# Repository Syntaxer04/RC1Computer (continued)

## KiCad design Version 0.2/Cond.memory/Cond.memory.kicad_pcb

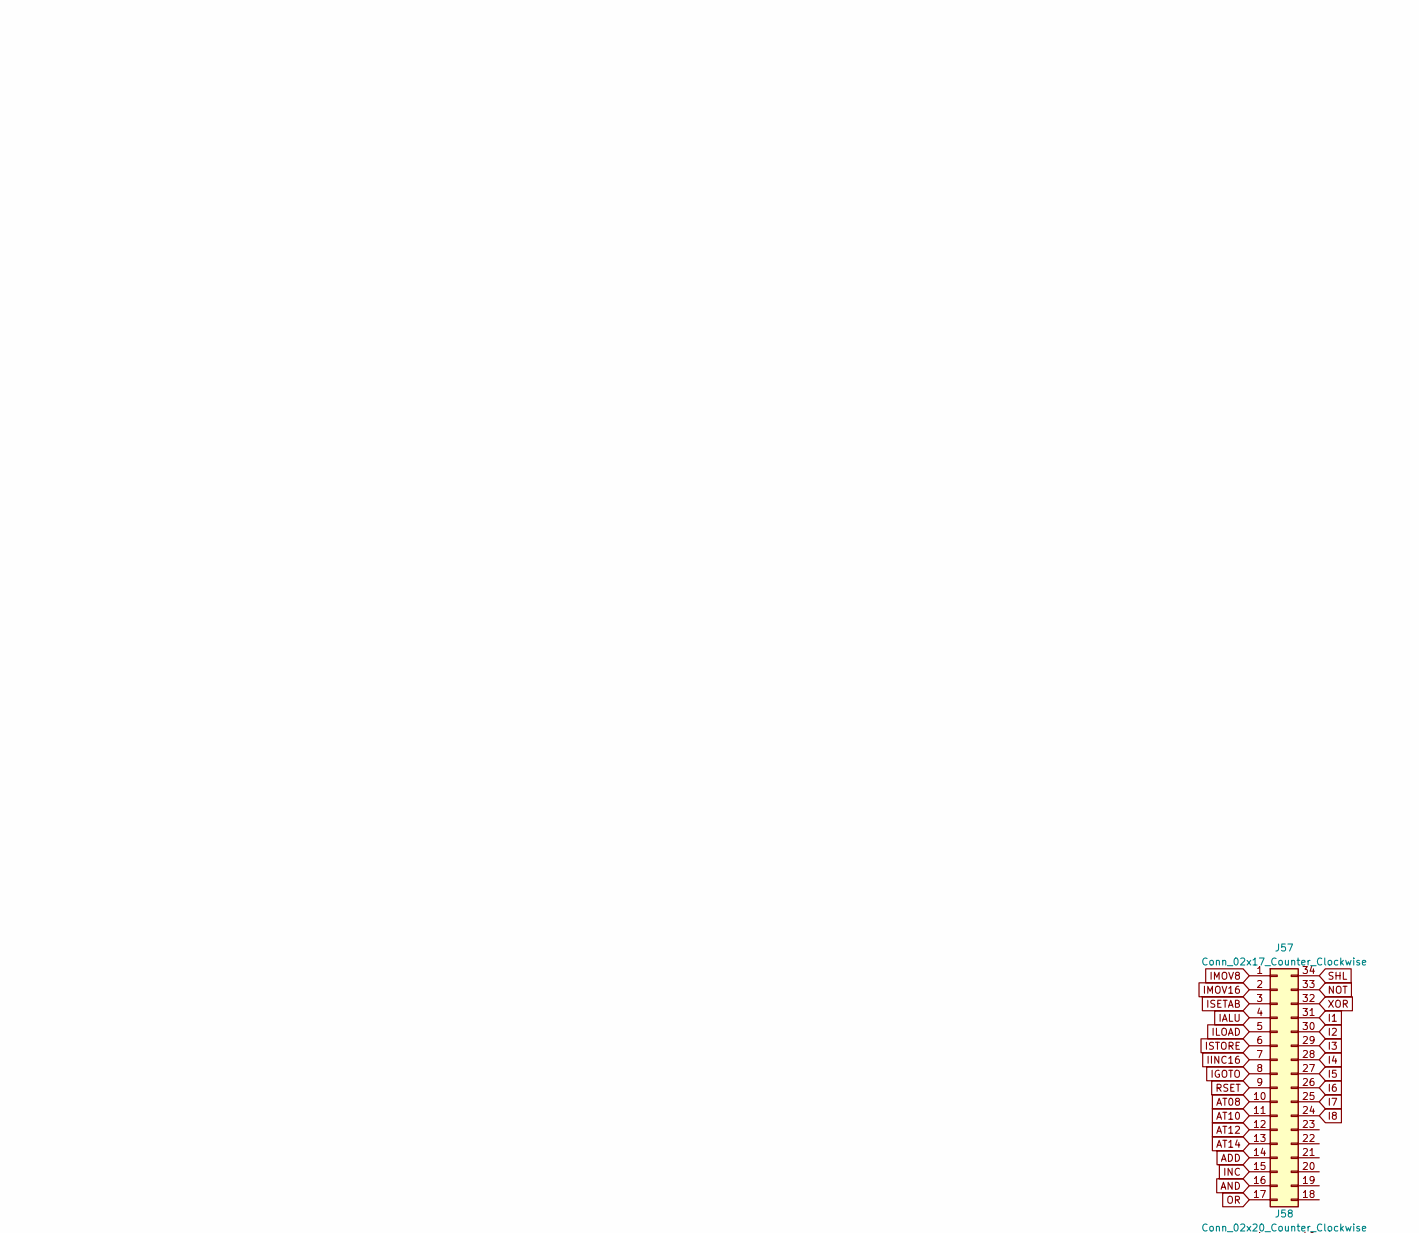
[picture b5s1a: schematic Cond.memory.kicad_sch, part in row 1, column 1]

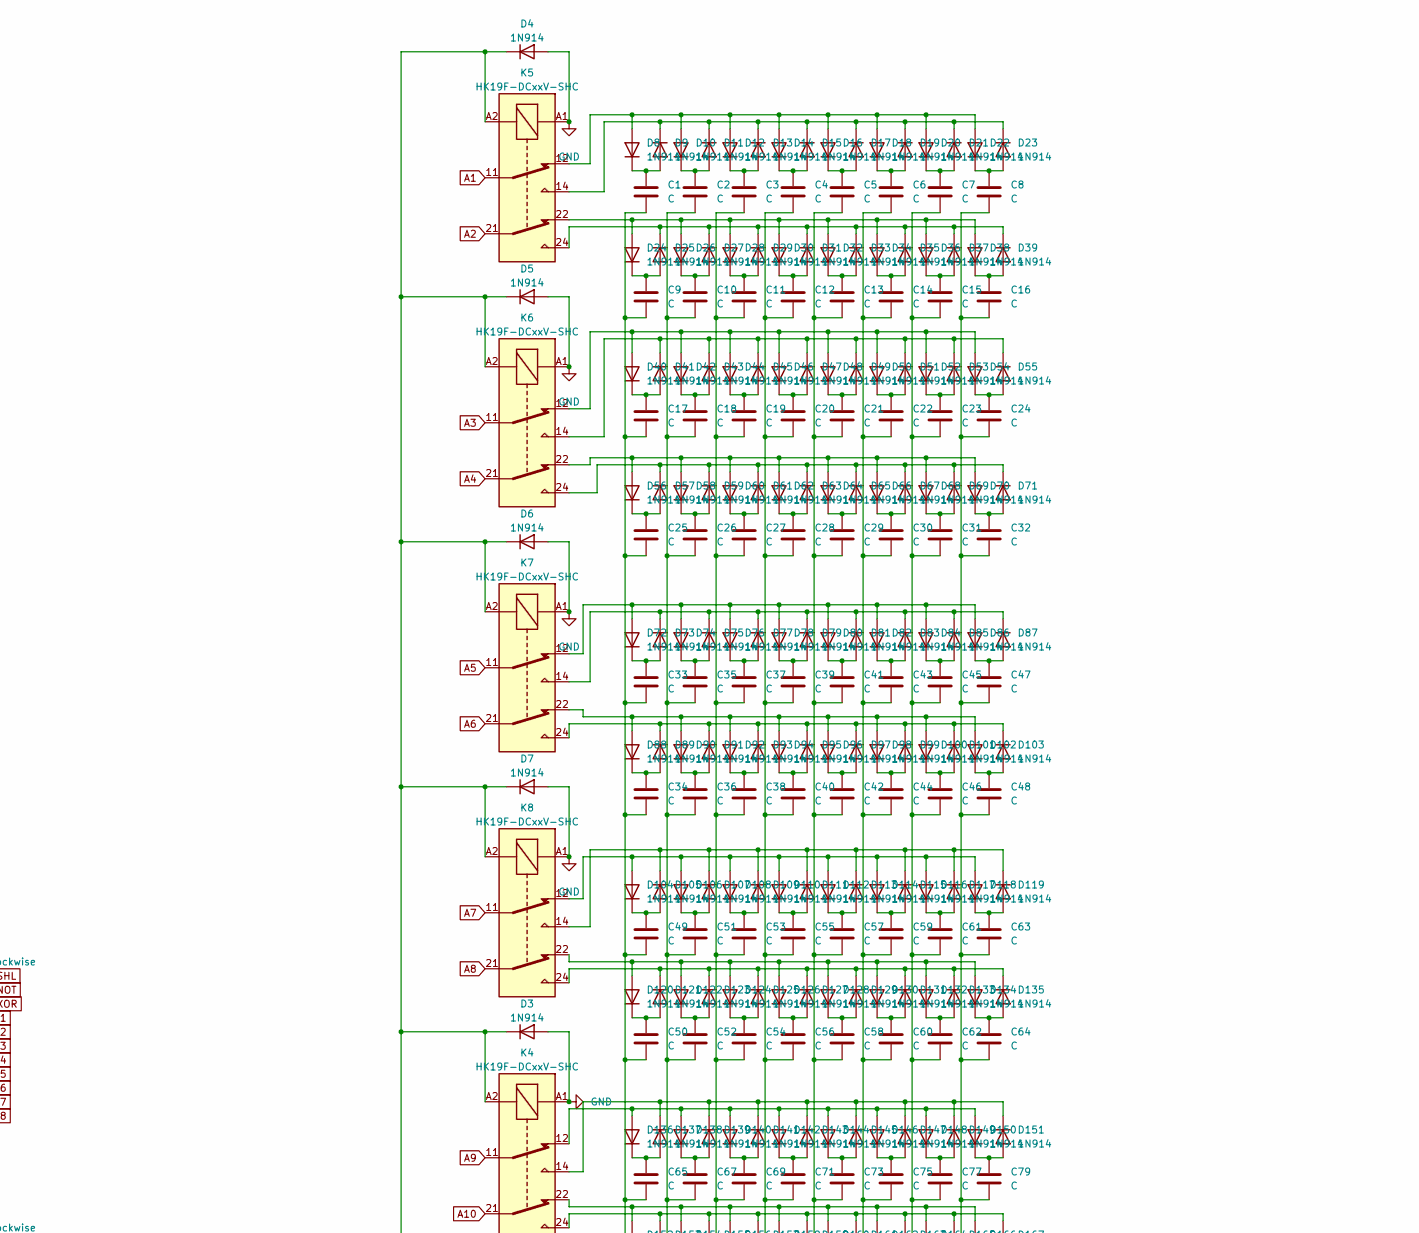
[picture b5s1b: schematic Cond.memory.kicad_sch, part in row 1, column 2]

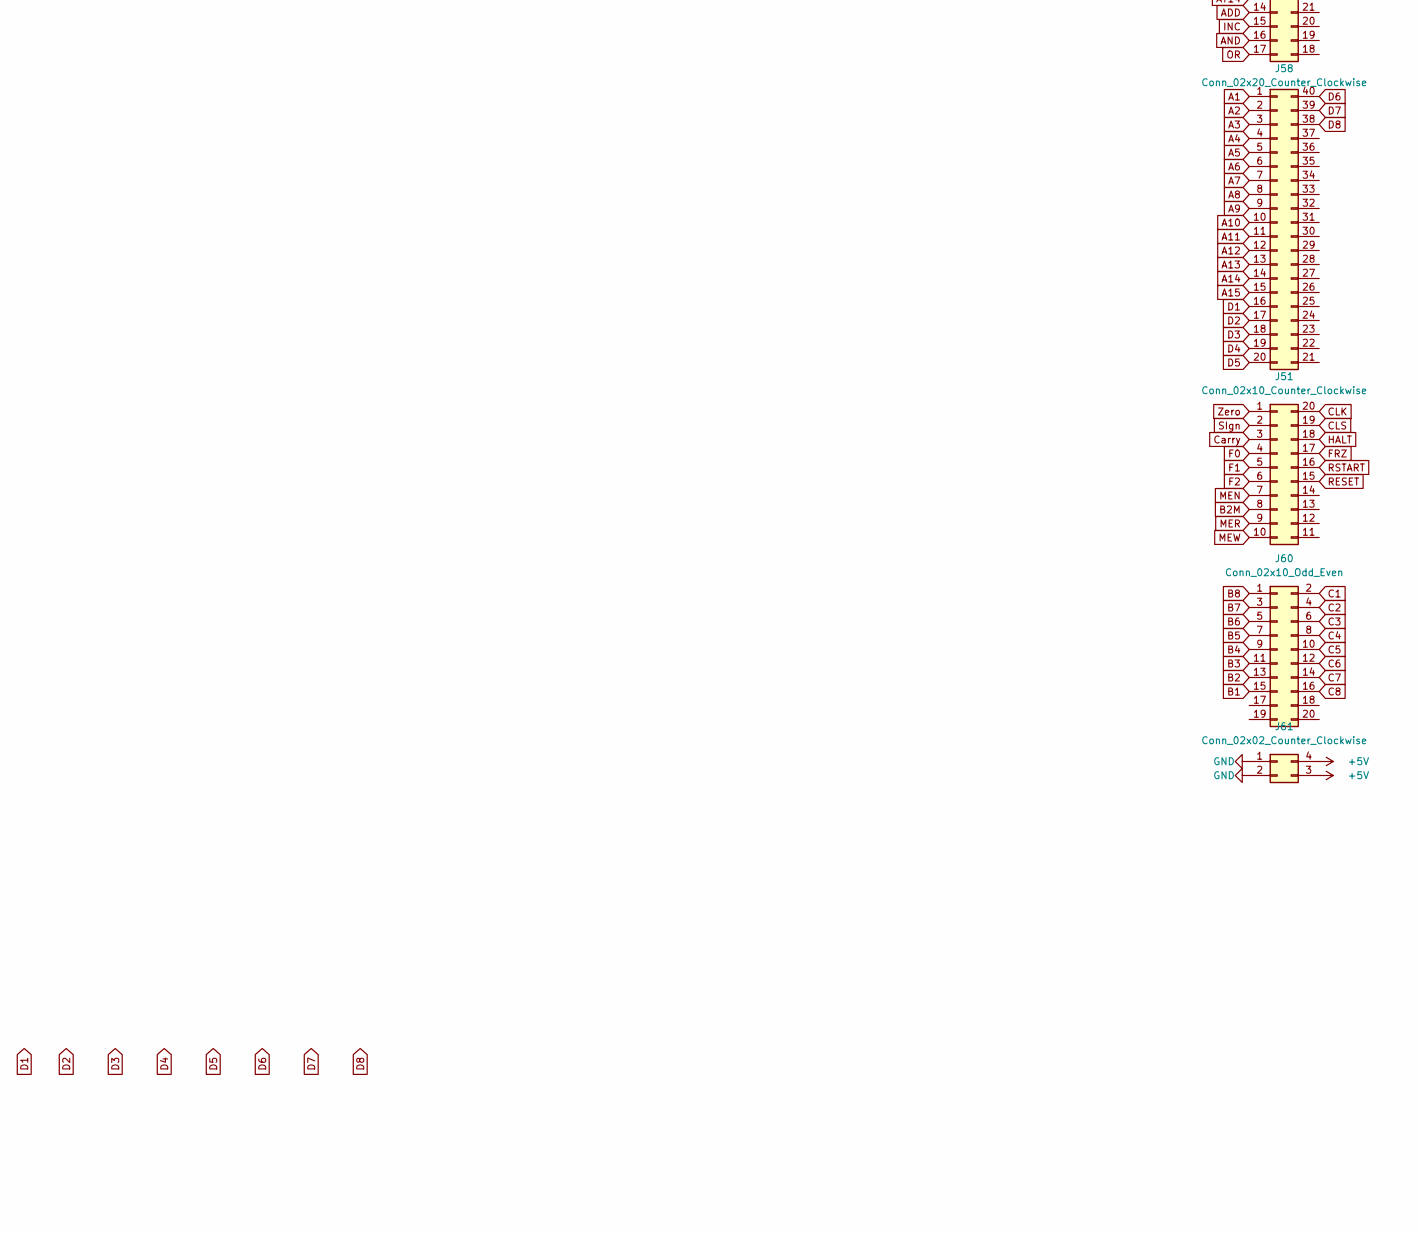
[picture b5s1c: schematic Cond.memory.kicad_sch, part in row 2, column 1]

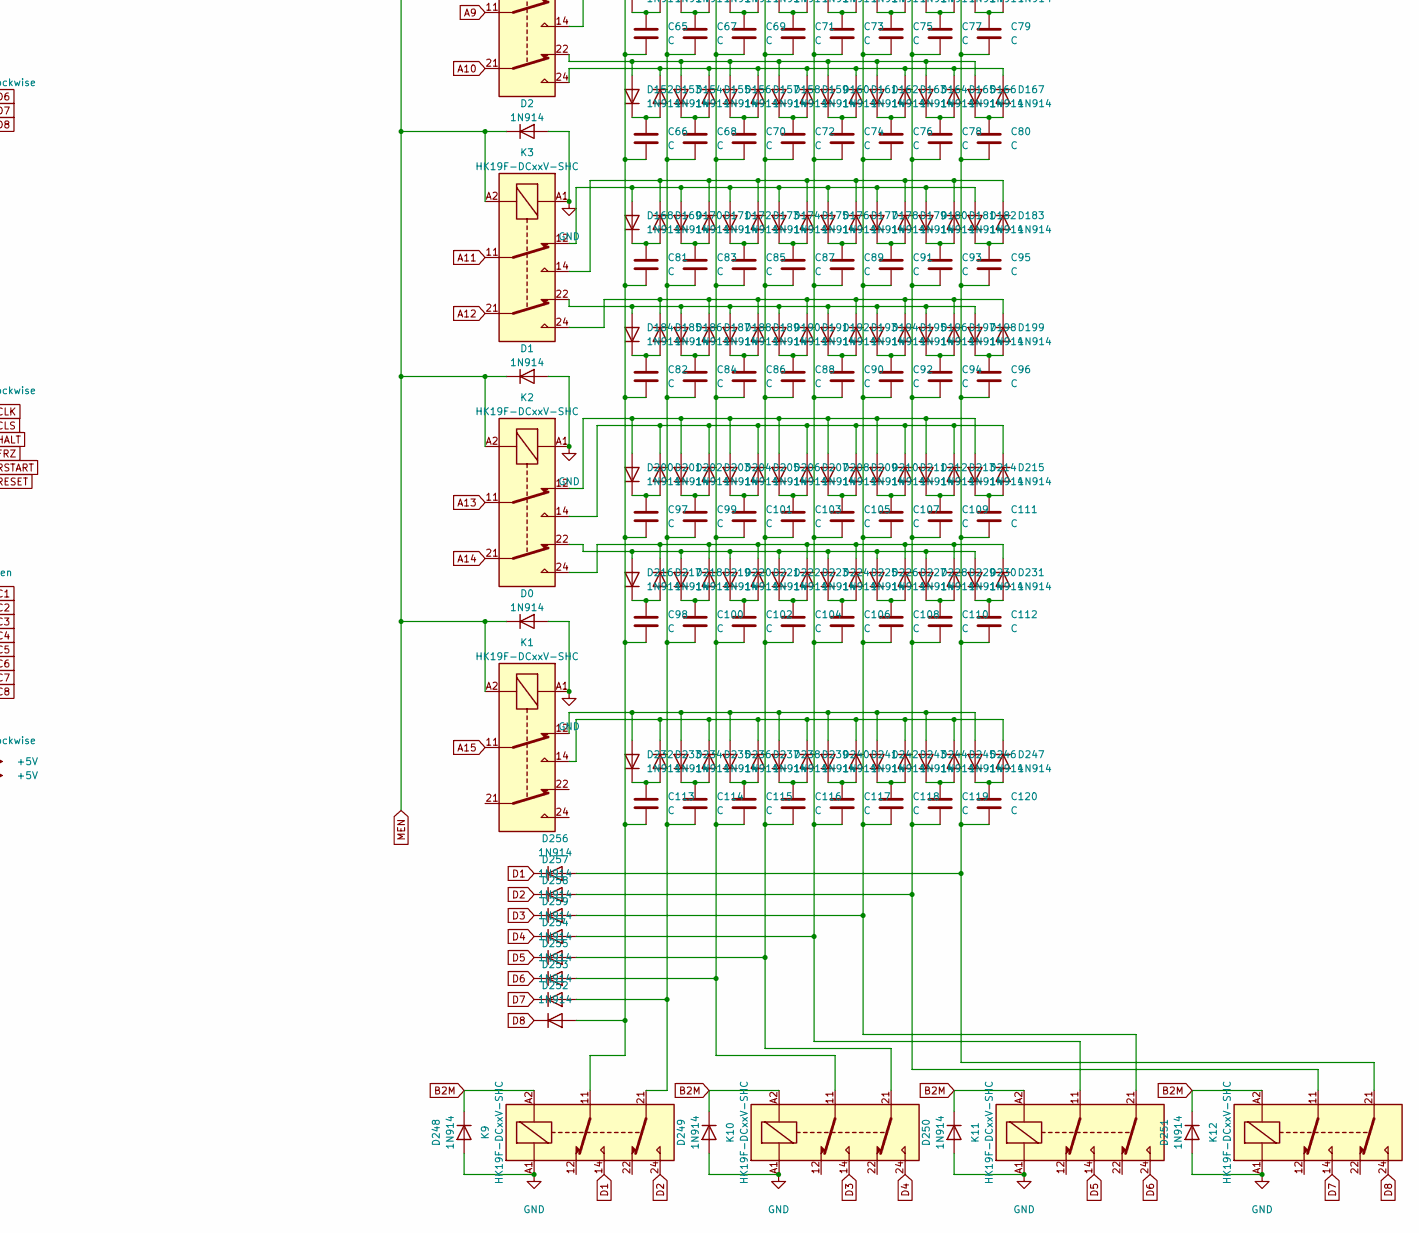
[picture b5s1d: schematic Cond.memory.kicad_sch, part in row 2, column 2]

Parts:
C1, C2, C3, C4, C5, C6, C7, C8, C9, C10, C11, C12, C13, C14, C15, C16, C17, C18, C19, C20, C21, C22, C23, C24, C25, C26, C27, C28, C29, C30, C31, C32, C33, C34, C35, C36, C37, C38, C39, C40, C41, C42, C43, C44, C45, C46, C47, C48, C49, C50, C51, C52, C53, C54, C55, C56, C57, C58, C59, C60, C61, C62, C63, C64, C65, C66, C67, C68, C69, C70, C71, C72, C73, C74, C75, C76, C77, C78, C79, C80, C81, C82, C83, C84, C85, C86, C87, C88, C89, C90, C91, C92, C93, C94, C95, C96, C97, C98, C99, C100, C101, C102, C103, C104, C105, C106, C107, C108, C109, C110, C111, C112, C113, C114, C115, C116, C117, C118, C119, C120: C; C_Radial_D10.0mm_H12.5mm_P5.00mm
D0, D1, D2, D3, D4, D5, D6, D7, D8, D9, D10, D11, D12, D13, D14, D15, D16, D17, D18, D19, D20, D21, D22, D23, D24, D25, D26, D27, D28, D29, D30, D31, D32, D33, D34, D35, D36, D37, D38, D39, D40, D41, D42, D43, D44, D45, D46, D47, D48, D49, D50, D51, D52, D53, D54, D55, D56, D57, D58, D59, D60, D61, D62, D63, D64, D65, D66, D67, D68, D69, D70, D71, D72, D73, D74, D75, D76, D77, D78, D79, D80, D81, D82, D83, D84, D85, D86, D87, D88, D89, D90, D91, D92, D93, D94, D95, D96, D97, D98, D99, D100, D101, D102, D103, D104, D105, D106, D107, D108, D109, D110, D111, D112, D113, D114, D115, D116, D117, D118, D119, D120, D121, D122, D123, D124, D125, D126, D127, D128, D129, D130, D131, D132, D133, D134, D135, D136, D137, D138, D139, D140, D141, D142, D143, D144, D145, D146, D147, D148, D149, D150, D151, D152, D153, D154, D155, D156, D157, D158, D159, D160, D161, D162, D163, D164, D165, D166, D167, D168, D169, D170, D171, D172, D173, D174, D175, D176, D177, D178, D179, D180, D181, D182, D183, D184, D185, D186, D187, D188, D189, D190, D191, D192, D193, D194, D195, D196, D197, D198, D199, D200, D201, D202, D203, D204, D205, D206, D207, D208, D209, D210, D211, D212, D213, D214, D215, D216, D217, D218, D219, D220, D221, D222, D223, D224, D225, D226, D227, D228, D229, D230, D231, D232, D233, D234, D235, D236, D237, D238, D239, D240, D241, D242, D243, D244, D245, D246, D247, D248, D249, D250, D251, D252, D253, D254, D255, D256, D257, D258, D259: 1N914; D_DO-35_SOD27_P7.62mm_Horizontal
J51: Conn_02x10_Counter_Clockwise; PinSocket_2x10_P2.54mm_Vertical
J57: Conn_02x17_Counter_Clockwise; PinSocket_2x17_P2.54mm_Vertical
J58: Conn_02x20_Counter_Clockwise; PinSocket_2x20_P2.54mm_Vertical
J60: Conn_02x10_Odd_Even; PinSocket_2x10_P2.54mm_Vertical
J61: Conn_02x02_Counter_Clockwise; PinSocket_2x02_P2.54mm_Vertical
K1, K2, K3, K4, K5, K6, K7, K8, K9, K10, K11, K12: HK19F-DCxxV-SHC; Relay_DPDT_Finder_30.22 ohne SilkS

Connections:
A1: J58.1, K5.11; also elsewhere on the board
A2: J58.2, K5.21; also elsewhere on the board
A3: J58.3, K6.11; also elsewhere on the board
A4: J58.4, K6.21; also elsewhere on the board
A5: J58.5, K7.11; also elsewhere on the board
A6: J58.6, K7.21; also elsewhere on the board
A7: J58.7, K8.11; also elsewhere on the board
A8: J58.8, K8.21; also elsewhere on the board
A9: J58.9, K4.11; also elsewhere on the board
A10: J58.10, K4.21; also elsewhere on the board
A11: J58.11, K3.11; also elsewhere on the board
A12: J58.12, K3.21; also elsewhere on the board
A13: J58.13, K2.11; also elsewhere on the board
A14: J58.14, K2.21; also elsewhere on the board
A15: J58.15, K1.11; also elsewhere on the board
B2M: D248.1 (K), D249.1 (K), D250.1 (K), D251.1 (K), J51.8, K9.A2, K10.A2, K11.A2, K12.A2
CLK: J51.20
CLS: J51.19
Carry: J51.3
D1: D256.1 (K), J58.16, K9.14; also elsewhere on the board
D2: D257.1 (K), J58.17, K9.24; also elsewhere on the board
D3: D258.1 (K), J58.18, K10.14; also elsewhere on the board
D4: D259.1 (K), J58.19, K10.24; also elsewhere on the board
D5: D254.1 (K), J58.20, K11.14; also elsewhere on the board
D6: D255.1 (K), J58.40, K11.24; also elsewhere on the board
D7: D253.1 (K), J58.39, K12.14; also elsewhere on the board
D8: D252.1 (K), J58.38, K12.24; also elsewhere on the board
F0: J51.4
F1: J51.5
F2: J51.6
FRZ: J51.17
GND: D0.2 (A), D1.2 (A), D2.2 (A), D3.2 (A), D4.2 (A), D5.2 (A), D6.2 (A), D7.2 (A), D248.2 (A), D249.2 (A), D250.2 (A), D251.2 (A), J61.1, J61.2, K1.A1, K2.A1, K3.A1, K4.A1, K5.A1, K6.A1, K7.A1, K8.A1, K9.A1, K10.A1, K11.A1, K12.A1; also elsewhere on the board
HALT: J51.18
MEN: D0.1 (K), D1.1 (K), D2.1 (K), D3.1 (K), D4.1 (K), D5.1 (K), D6.1 (K), D7.1 (K), J51.7, K1.A2, K2.A2, K3.A2, K4.A2, K5.A2, K6.A2, K7.A2, K8.A2
MER: J51.9
MEW: J51.10
unnamed: C1.1, D8.1 (K), D9.2 (A)
unnamed: D8.2 (A), D10.2 (A), D12.2 (A), D14.2 (A), D16.2 (A), D18.2 (A), D20.2 (A), D22.2 (A), K5.12
unnamed: C2.1, D10.1 (K), D11.2 (A)
unnamed: D9.1 (K), D11.1 (K), D13.1 (K), D15.1 (K), D17.1 (K), D19.1 (K), D21.1 (K), D23.1 (K), K5.14
unnamed: C3.1, D12.1 (K), D13.2 (A)
unnamed: C4.1, D14.1 (K), D15.2 (A)
unnamed: C5.1, D16.1 (K), D17.2 (A)
unnamed: C6.1, D18.1 (K), D19.2 (A)
unnamed: C7.1, D20.1 (K), D21.2 (A)
unnamed: C8.1, D22.1 (K), D23.2 (A)
unnamed: D24.2 (A), D26.2 (A), D28.2 (A), D30.2 (A), D32.2 (A), D34.2 (A), D36.2 (A), D38.2 (A), K5.22
unnamed: C9.1, D24.1 (K), D25.2 (A)
unnamed: D25.1 (K), D27.1 (K), D29.1 (K), D31.1 (K), D33.1 (K), D35.1 (K), D37.1 (K), D39.1 (K), K5.24
unnamed: C10.1, D26.1 (K), D27.2 (A)
unnamed: C11.1, D28.1 (K), D29.2 (A)
unnamed: C12.1, D30.1 (K), D31.2 (A)
unnamed: C13.1, D32.1 (K), D33.2 (A)
unnamed: C14.1, D34.1 (K), D35.2 (A)
unnamed: C15.1, D36.1 (K), D37.2 (A)
unnamed: C16.1, D38.1 (K), D39.2 (A)
unnamed: D40.2 (A), D42.2 (A), D44.2 (A), D46.2 (A), D48.2 (A), D50.2 (A), D52.2 (A), D54.2 (A), K6.12
unnamed: C17.1, D40.1 (K), D41.2 (A)
unnamed: D41.1 (K), D43.1 (K), D45.1 (K), D47.1 (K), D49.1 (K), D51.1 (K), D53.1 (K), D55.1 (K), K6.14
unnamed: C18.1, D42.1 (K), D43.2 (A)
unnamed: C19.1, D44.1 (K), D45.2 (A)
unnamed: C20.1, D46.1 (K), D47.2 (A)
unnamed: C21.1, D48.1 (K), D49.2 (A)
unnamed: C22.1, D50.1 (K), D51.2 (A)
unnamed: C23.1, D52.1 (K), D53.2 (A)
unnamed: C24.1, D54.1 (K), D55.2 (A)
unnamed: D56.2 (A), D58.2 (A), D60.2 (A), D62.2 (A), D64.2 (A), D66.2 (A), D68.2 (A), D70.2 (A), K6.22
unnamed: C25.1, D56.1 (K), D57.2 (A)
unnamed: D57.1 (K), D59.1 (K), D61.1 (K), D63.1 (K), D65.1 (K), D67.1 (K), D69.1 (K), D71.1 (K), K6.24
unnamed: C26.1, D58.1 (K), D59.2 (A)
unnamed: C27.1, D60.1 (K), D61.2 (A)
unnamed: C28.1, D62.1 (K), D63.2 (A)
unnamed: C29.1, D64.1 (K), D65.2 (A)
unnamed: C30.1, D66.1 (K), D67.2 (A)
unnamed: C31.1, D68.1 (K), D69.2 (A)
unnamed: C32.1, D70.1 (K), D71.2 (A)
unnamed: D72.2 (A), D74.2 (A), D76.2 (A), D78.2 (A), D80.2 (A), D82.2 (A), D84.2 (A), D86.2 (A), K7.12
unnamed: C33.1, D72.1 (K), D73.2 (A)
unnamed: D73.1 (K), D75.1 (K), D77.1 (K), D79.1 (K), D81.1 (K), D83.1 (K), D85.1 (K), D87.1 (K), K7.14
unnamed: C35.1, D74.1 (K), D75.2 (A)
unnamed: C37.1, D76.1 (K), D77.2 (A)
unnamed: C39.1, D78.1 (K), D79.2 (A)
unnamed: C41.1, D80.1 (K), D81.2 (A)
unnamed: C43.1, D82.1 (K), D83.2 (A)
unnamed: C45.1, D84.1 (K), D85.2 (A)
unnamed: C47.1, D86.1 (K), D87.2 (A)
unnamed: C34.1, D88.1 (K), D89.2 (A)
unnamed: C36.1, D90.1 (K), D91.2 (A)
unnamed: C38.1, D92.1 (K), D93.2 (A)
unnamed: C40.1, D94.1 (K), D95.2 (A)
unnamed: C42.1, D96.1 (K), D97.2 (A)
unnamed: C44.1, D98.1 (K), D99.2 (A)
unnamed: D88.2 (A), D90.2 (A), D92.2 (A), D94.2 (A), D96.2 (A), D98.2 (A), D100.2 (A), D102.2 (A), K7.22
unnamed: C46.1, D100.1 (K), D101.2 (A)
unnamed: D89.1 (K), D91.1 (K), D93.1 (K), D95.1 (K), D97.1 (K), D99.1 (K), D101.1 (K), D103.1 (K), K7.24
unnamed: C48.1, D102.1 (K), D103.2 (A)
unnamed: D104.2 (A), D106.2 (A), D108.2 (A), D110.2 (A), D112.2 (A), D114.2 (A), D116.2 (A), D118.2 (A), K8.12
unnamed: C49.1, D104.1 (K), D105.2 (A)
unnamed: D105.1 (K), D107.1 (K), D109.1 (K), D111.1 (K), D113.1 (K), D115.1 (K), D117.1 (K), D119.1 (K), K8.14
unnamed: C51.1, D106.1 (K), D107.2 (A)
unnamed: C53.1, D108.1 (K), D109.2 (A)
unnamed: C55.1, D110.1 (K), D111.2 (A)
unnamed: C57.1, D112.1 (K), D113.2 (A)
unnamed: C59.1, D114.1 (K), D115.2 (A)
unnamed: C61.1, D116.1 (K), D117.2 (A)
unnamed: C63.1, D118.1 (K), D119.2 (A)
unnamed: D120.2 (A), D122.2 (A), D124.2 (A), D126.2 (A), D128.2 (A), D130.2 (A), D132.2 (A), D134.2 (A), K8.22
unnamed: C50.1, D120.1 (K), D121.2 (A)
unnamed: D121.1 (K), D123.1 (K), D125.1 (K), D127.1 (K), D129.1 (K), D131.1 (K), D133.1 (K), D135.1 (K), K8.24
unnamed: C52.1, D122.1 (K), D123.2 (A)
unnamed: C54.1, D124.1 (K), D125.2 (A)
unnamed: C56.1, D126.1 (K), D127.2 (A)
unnamed: C58.1, D128.1 (K), D129.2 (A)
unnamed: C60.1, D130.1 (K), D131.2 (A)
unnamed: C62.1, D132.1 (K), D133.2 (A)
unnamed: C64.1, D134.1 (K), D135.2 (A)
unnamed: D136.2 (A), D138.2 (A), D140.2 (A), D142.2 (A), D144.2 (A), D146.2 (A), D148.2 (A), D150.2 (A), K4.12
unnamed: C65.1, D136.1 (K), D137.2 (A)
unnamed: D137.1 (K), D139.1 (K), D141.1 (K), D143.1 (K), D145.1 (K), D147.1 (K), D149.1 (K), D151.1 (K), K4.14
unnamed: C67.1, D138.1 (K), D139.2 (A)
unnamed: C69.1, D140.1 (K), D141.2 (A)
unnamed: C71.1, D142.1 (K), D143.2 (A)
unnamed: C73.1, D144.1 (K), D145.2 (A)
unnamed: C75.1, D146.1 (K), D147.2 (A)
unnamed: C77.1, D148.1 (K), D149.2 (A)
unnamed: C79.1, D150.1 (K), D151.2 (A)
unnamed: D152.2 (A), D154.2 (A), D156.2 (A), D158.2 (A), D160.2 (A), D162.2 (A), D164.2 (A), D166.2 (A), K4.22
unnamed: C66.1, D152.1 (K), D153.2 (A)
unnamed: D153.1 (K), D155.1 (K), D157.1 (K), D159.1 (K), D161.1 (K), D163.1 (K), D165.1 (K), D167.1 (K), K4.24
unnamed: C68.1, D154.1 (K), D155.2 (A)
unnamed: C70.1, D156.1 (K), D157.2 (A)
unnamed: C72.1, D158.1 (K), D159.2 (A)
unnamed: C74.1, D160.1 (K), D161.2 (A)
unnamed: C76.1, D162.1 (K), D163.2 (A)
unnamed: C78.1, D164.1 (K), D165.2 (A)
unnamed: C80.1, D166.1 (K), D167.2 (A)
unnamed: D168.2 (A), D170.2 (A), D172.2 (A), D174.2 (A), D176.2 (A), D178.2 (A), D180.2 (A), D182.2 (A), K3.12
unnamed: C81.1, D168.1 (K), D169.2 (A)
unnamed: D169.1 (K), D171.1 (K), D173.1 (K), D175.1 (K), D177.1 (K), D179.1 (K), D181.1 (K), D183.1 (K), K3.14
unnamed: C83.1, D170.1 (K), D171.2 (A)
unnamed: C85.1, D172.1 (K), D173.2 (A)
unnamed: C87.1, D174.1 (K), D175.2 (A)
unnamed: C89.1, D176.1 (K), D177.2 (A)
unnamed: C91.1, D178.1 (K), D179.2 (A)
unnamed: C93.1, D180.1 (K), D181.2 (A)
unnamed: C95.1, D182.1 (K), D183.2 (A)
unnamed: D184.2 (A), D186.2 (A), D188.2 (A), D190.2 (A), D192.2 (A), D194.2 (A), D196.2 (A), D198.2 (A), K3.22
unnamed: C82.1, D184.1 (K), D185.2 (A)
unnamed: D185.1 (K), D187.1 (K), D189.1 (K), D191.1 (K), D193.1 (K), D195.1 (K), D197.1 (K), D199.1 (K), K3.24
unnamed: C84.1, D186.1 (K), D187.2 (A)
unnamed: C86.1, D188.1 (K), D189.2 (A)
unnamed: C88.1, D190.1 (K), D191.2 (A)
unnamed: C90.1, D192.1 (K), D193.2 (A)
unnamed: C92.1, D194.1 (K), D195.2 (A)
unnamed: C94.1, D196.1 (K), D197.2 (A)
unnamed: C96.1, D198.1 (K), D199.2 (A)
unnamed: D200.2 (A), D202.2 (A), D204.2 (A), D206.2 (A), D208.2 (A), D210.2 (A), D212.2 (A), D214.2 (A), K2.12
unnamed: C97.1, D200.1 (K), D201.2 (A)
unnamed: D201.1 (K), D203.1 (K), D205.1 (K), D207.1 (K), D209.1 (K), D211.1 (K), D213.1 (K), D215.1 (K), K2.14
unnamed: C99.1, D202.1 (K), D203.2 (A)
unnamed: C101.1, D204.1 (K), D205.2 (A)
unnamed: C103.1, D206.1 (K), D207.2 (A)
unnamed: C105.1, D208.1 (K), D209.2 (A)
unnamed: C107.1, D210.1 (K), D211.2 (A)
unnamed: C109.1, D212.1 (K), D213.2 (A)
unnamed: C111.1, D214.1 (K), D215.2 (A)
unnamed: D216.2 (A), D218.2 (A), D220.2 (A), D222.2 (A), D224.2 (A), D226.2 (A), D228.2 (A), D230.2 (A), K2.22
unnamed: C98.1, D216.1 (K), D217.2 (A)
unnamed: D217.1 (K), D219.1 (K), D221.1 (K), D223.1 (K), D225.1 (K), D227.1 (K), D229.1 (K), D231.1 (K), K2.24
unnamed: C100.1, D218.1 (K), D219.2 (A)
unnamed: C102.1, D220.1 (K), D221.2 (A)
unnamed: C104.1, D222.1 (K), D223.2 (A)
unnamed: C106.1, D224.1 (K), D225.2 (A)
unnamed: C108.1, D226.1 (K), D227.2 (A)
unnamed: C110.1, D228.1 (K), D229.2 (A)
unnamed: C112.1, D230.1 (K), D231.2 (A)
unnamed: D232.2 (A), D234.2 (A), D236.2 (A), D238.2 (A), D240.2 (A), D242.2 (A), D244.2 (A), D246.2 (A), K1.12
unnamed: C113.1, D232.1 (K), D233.2 (A)
unnamed: D233.1 (K), D235.1 (K), D237.1 (K), D239.1 (K), D241.1 (K), D243.1 (K), D245.1 (K), D247.1 (K), K1.14
unnamed: C114.1, D234.1 (K), D235.2 (A)
unnamed: C115.1, D236.1 (K), D237.2 (A)
unnamed: C116.1, D238.1 (K), D239.2 (A)
unnamed: C117.1, D240.1 (K), D241.2 (A)
unnamed: C118.1, D242.1 (K), D243.2 (A)
unnamed: C119.1, D244.1 (K), D245.2 (A)
unnamed: C120.1, D246.1 (K), D247.2 (A)
unnamed: C1.2, C9.2, C17.2, C25.2, C33.2, C34.2, C49.2, C50.2, C65.2, C66.2, C81.2, C82.2, C97.2, C98.2, C113.2, D252.2 (A), K9.11
unnamed: C2.2, C10.2, C18.2, C26.2, C35.2, C36.2, C51.2, C52.2, C67.2, C68.2, C83.2, C84.2, C99.2, C100.2, C114.2, D253.2 (A), K9.21
unnamed: C4.2, C12.2, C20.2, C28.2, C39.2, C40.2, C55.2, C56.2, C71.2, C72.2, C87.2, C88.2, C103.2, C104.2, C116.2, D254.2 (A), K10.21
unnamed: C3.2, C11.2, C19.2, C27.2, C37.2, C38.2, C53.2, C54.2, C69.2, C70.2, C85.2, C86.2, C101.2, C102.2, C115.2, D255.2 (A), K10.11
unnamed: C8.2, C16.2, C24.2, C32.2, C47.2, C48.2, C63.2, C64.2, C79.2, C80.2, C95.2, C96.2, C111.2, C112.2, C120.2, D256.2 (A), K12.21
unnamed: C7.2, C15.2, C23.2, C31.2, C45.2, C46.2, C61.2, C62.2, C77.2, C78.2, C93.2, C94.2, C109.2, C110.2, C119.2, D257.2 (A), K12.11
unnamed: C6.2, C14.2, C22.2, C30.2, C43.2, C44.2, C59.2, C60.2, C75.2, C76.2, C91.2, C92.2, C107.2, C108.2, C118.2, D258.2 (A), K11.21
unnamed: C5.2, C13.2, C21.2, C29.2, C41.2, C42.2, C57.2, C58.2, C73.2, C74.2, C89.2, C90.2, C105.2, C106.2, C117.2, D259.2 (A), K11.11
unnamed: J61.3, J61.4
RESET: J51.15
RSTART: J51.16
SIgn: J51.2
Zero: J51.1

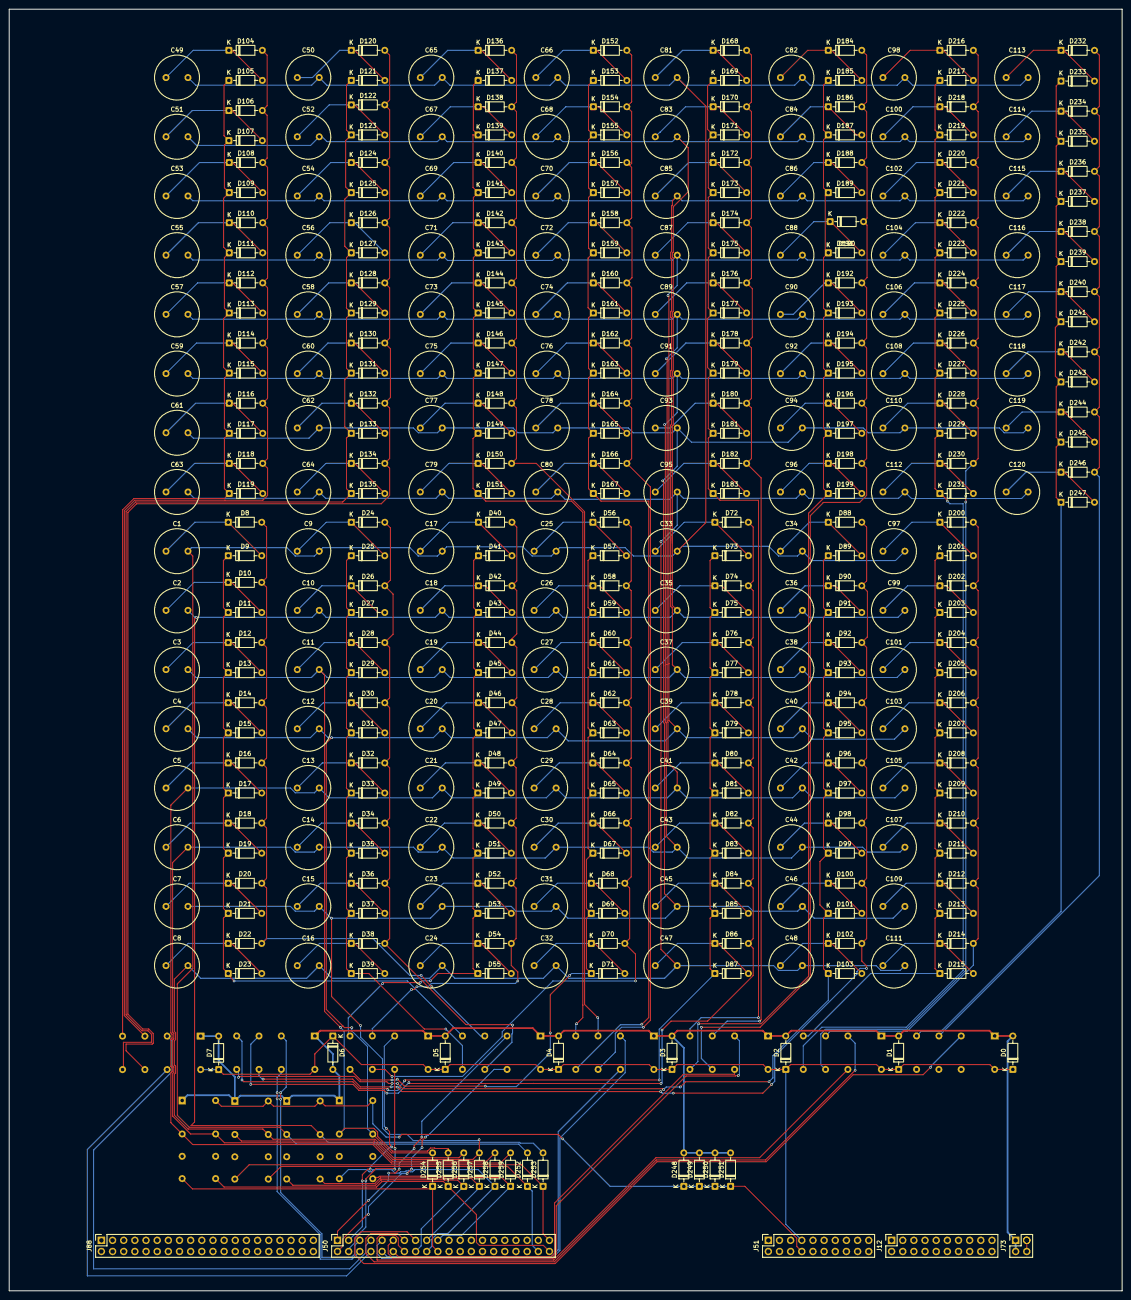
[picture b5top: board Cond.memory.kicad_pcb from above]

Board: 2 copper layers, 253.4 x 291.8 mm, 397 parts (0 on the bottom side), 185 nets.

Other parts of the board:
J12: Conn_02x10_Odd_Even; PinSocket_2x10_P2.54mm_Vertical
J50, J88: Conn_02x20_Counter_Clockwise; PinSocket_2x20_P2.54mm_Vertical
J73: Conn_02x02_Counter_Clockwise; PinSocket_2x02_P2.54mm_Vertical

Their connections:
+5V: J73.3, J73.4
A1: J50.1; also elsewhere on the board
A2: J50.2; also elsewhere on the board
A3: J50.3; also elsewhere on the board
A4: J50.4; also elsewhere on the board
A5: J50.5; also elsewhere on the board
A6: J50.6; also elsewhere on the board
A7: J50.7; also elsewhere on the board
A8: J50.8; also elsewhere on the board
A9: J50.9; also elsewhere on the board
A10: J50.10; also elsewhere on the board
A11: J50.11; also elsewhere on the board
A12: J50.12; also elsewhere on the board
A13: J50.13; also elsewhere on the board
A14: J50.14; also elsewhere on the board
A15: J50.15; also elsewhere on the board
D1: J50.16; also elsewhere on the board
D2: J50.17; also elsewhere on the board
D3: J50.18; also elsewhere on the board
D4: J50.19; also elsewhere on the board
D5: J50.20; also elsewhere on the board
D6: J50.40; also elsewhere on the board
D7: J50.39; also elsewhere on the board
D8: J50.38; also elsewhere on the board
GND: J73.1, J73.2; also elsewhere on the board
